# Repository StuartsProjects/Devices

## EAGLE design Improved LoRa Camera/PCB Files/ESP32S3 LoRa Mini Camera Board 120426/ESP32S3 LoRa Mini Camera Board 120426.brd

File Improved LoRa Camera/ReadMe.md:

This is a repository for information on improved LoRa Camera boards. 

### Stuart Robinson

### April 2026

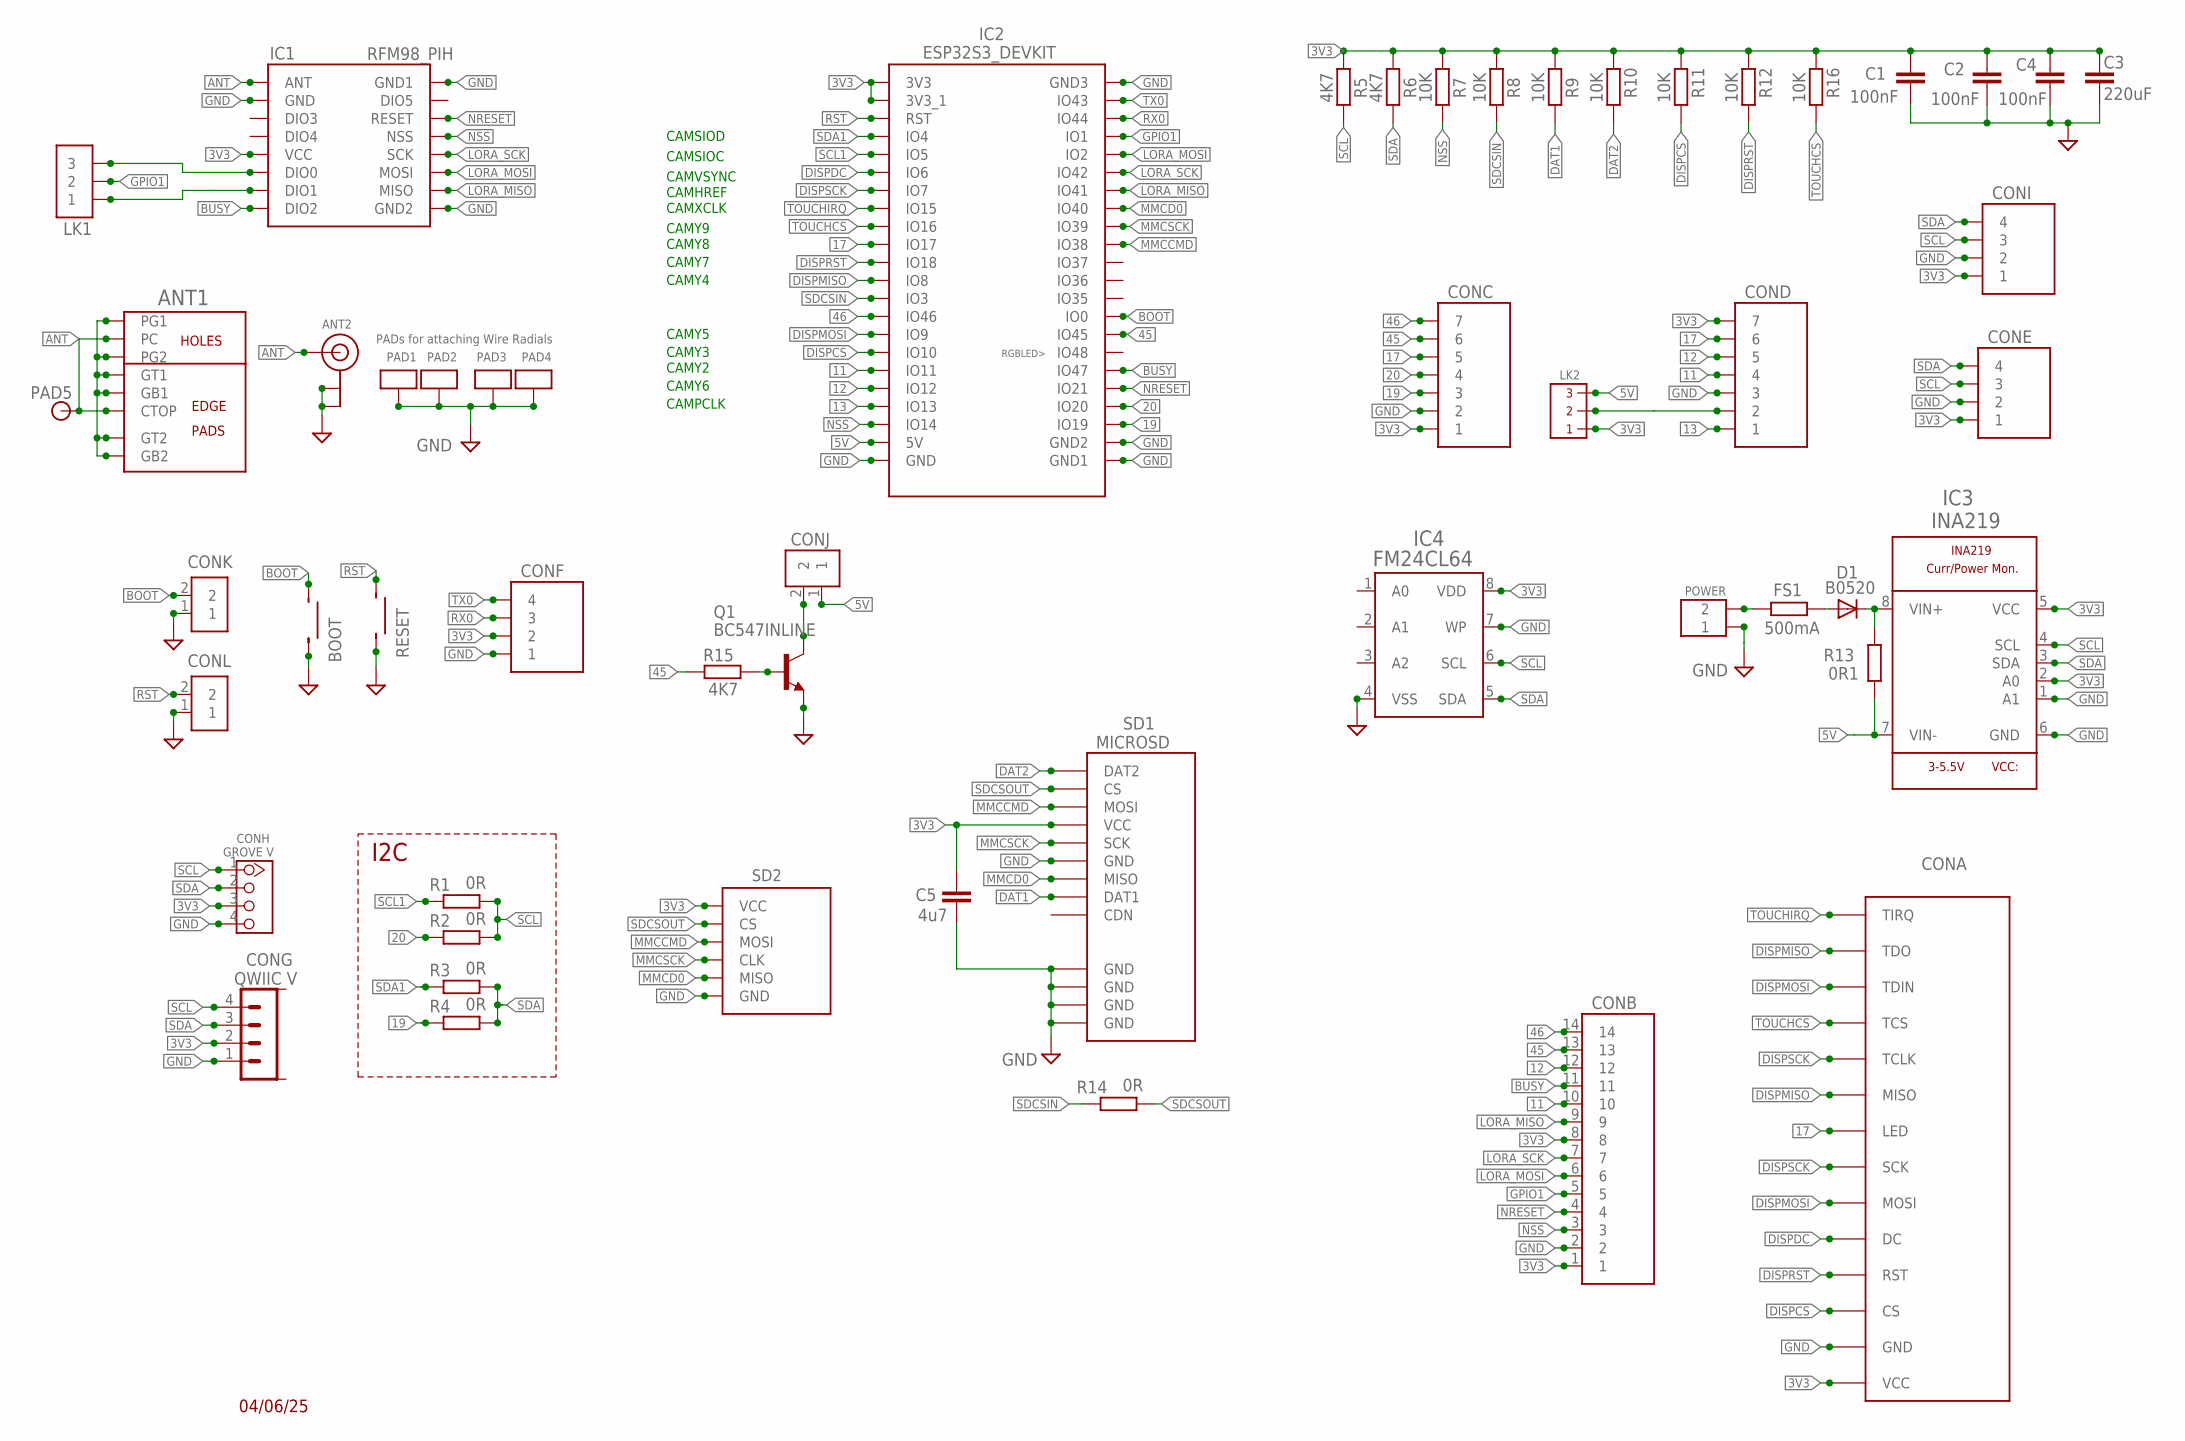
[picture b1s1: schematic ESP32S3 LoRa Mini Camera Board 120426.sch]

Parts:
ANT1: CUSTOMSMA
ANT2: ANTENNA_U.FL; U.FL
BOOT: SMALLSMTSWITCH
C1, C2, C4: 100nF; C1206
C3: 220uF; C1210K
C5: 4u7; C1206
CONA: ILI9341; ILI9341_2_4_INCH_NOSD
CONB: 14X1
CONC: 7X1STD; 7X1
COND: 7X1STD; 7X1
CONE: 4X1
CONF: 4X1
CONG: QWIIC V; BM04B-SRSS-TB
CONH: GROVE V; HW4-2.0
CONI: 4X1
CONJ: 2X1
CONK: 2X1
CONL: 2X1
D1: B0520; SOD123
FS1: 500mA; M1206
IC1: RFM98_PIH
IC2: ESP32S3_DEVKIT
IC3: INA219; SOIC8
IC4: FM24CL64; SOIC_2
LK1: 3X1
LK2: 3PINMICROHEADER_ROUND2; 3PINMICROHEADER_SMALL_ROUND_2
PAD1, PAD2, PAD3, PAD4: ANTPAD2
PAD5: PAD_ROUND_0_6MM_HOLE; PAD-ROUND_0_6MM_HOLE
POWER: SCREWTERMINAL_2WAY_0_1_INCH
Q1: BC547INLINE; TO92-CBE
R1, R2, R3, R4, R14: 0R; M1206
R5, R6, R15: 4K7; M1206
R7, R8, R9, R10, R11, R12, R16: 10K; M1206
R13: 0R1; R1206
RESET: SMALLSMTSWITCH
SD1: MICROSD; MICROSD_PP
SD2: MICROSD_BREAKOUT2_DEFAULT; MICROSD_BREAKOUT2

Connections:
3V3: C1.2, C2.2, C3.1, C4.2, C5.1, CONA.VCC, CONB.1, CONB.8, CONC.1, COND.7, CONE.1, CONF.2, CONG.2, CONH.3, CONI.1, IC1.VCC, IC2.3V3, IC2.3V3_1, IC3.2 (A0), IC3.5 (VCC), IC4.8 (VDD), LK2.1, R5.2, R6.2, R7.2, R8.2, R9.2, R10.2, R11.2, R12.2, R16.2, SD1.VCC, SD2.VCC
5V: CONJ.1, IC2.5V, IC3.7 (VIN-), LK2.3, R13.1
11: CONB.10, COND.4, IC2.11 (IO11)
12: CONB.12, COND.5, IC2.12 (IO12)
13: COND.1, IC2.13 (IO13)
17: CONA.LED, CONC.5, COND.6, IC2.17 (IO17)
19: CONC.3, IC2.19 (IO19), R4.2
20: CONC.4, IC2.20 (IO20), R2.2
45: CONB.13, CONC.6, IC2.45 (IO45), R15.2
46: CONB.14, CONC.7, IC2.46 (IO46)
ANT: ANT1.CTOP, ANT1.PC, ANT2.3 (SIGNAL), IC1.ANT, PAD5.P$1
BOOT: BOOT.P$4, CONK.2, IC2.0 (IO0)
BUSY: CONB.11, IC1.DIO2, IC2.47 (IO47)
DAT1: R9.1, SD1.DAT1
DAT2: R10.1, SD1.DAT2
DISPCS: CONA.CS, IC2.10 (IO10), R11.1
DISPDC: CONA.DC, IC2.6 (IO6)
DISPMISO: CONA.MISO, CONA.TDO, IC2.8 (IO8)
DISPMOSI: CONA.MOSI, CONA.TDIN, IC2.9 (IO9)
DISPRST: CONA.RST, IC2.18 (IO18), R12.1
DISPSCK: CONA.SCK, CONA.TCLK, IC2.7 (IO7)
GND: ANT1.G1, ANT1.G2, ANT1.GB1, ANT1.GB2, ANT1.GT1, ANT1.GT2, ANT2.1 (GND), ANT2.2 (GND), BOOT.P$3, C1.1, C2.1, C3.2, C4.1, C5.2, CONA.GND, CONB.2, CONC.2, COND.3, CONE.2, CONF.1, CONG.1, CONH.4, CONI.2, CONK.1, CONL.1, IC1.GND, IC1.GND1, IC1.GND2, IC2.GND, IC2.GND1, IC2.GND2, IC2.GND3, IC3.1 (A1), IC3.6 (GND), IC4.4 (VSS), IC4.7 (WP), PAD1.P$1, PAD2.P$1, PAD3.P$1, PAD4.P$1, POWER.P$1 (1), Q1.E, RESET.P$3, SD1.GND, SD1.GND@1 (GND), SD1.GND@2 (GND), SD1.GND@3 (GND), SD1.GND@4 (GND), SD2.GND
GPIO1: CONB.5, IC2.1 (IO1), LK1.2
LORA_MISO: CONB.9, IC1.MISO, IC2.41 (IO41)
LORA_MOSI: CONB.6, IC1.MOSI, IC2.2 (IO2)
LORA_SCK: CONB.7, IC1.SCK, IC2.42 (IO42)
MMCCMD: IC2.38 (IO38), SD1.MOSI, SD2.MOSI
MMCD0: IC2.40 (IO40), SD1.MISO, SD2.MISO
MMCSCK: IC2.39 (IO39), SD1.SCK, SD2.SCK (CLK)
unnamed: D1.C, IC3.8 (VIN+), R13.2
unnamed: IC1.DIO0, LK1.3
unnamed: FS1.1, POWER.P$2 (2)
unnamed: IC1.DIO1, LK1.1
unnamed: D1.A, FS1.2
unnamed: Q1.B, R15.1
unnamed: CONJ.2, Q1.C
unnamed: COND.2, LK2.2
NRESET: CONB.4, IC1.RESET, IC2.21 (IO21)
NSS: CONB.3, IC1.NSS, IC2.14 (IO14), R7.1
RST: CONL.2, IC2.RST, RESET.P$4
RX0: CONF.3, IC2.44 (IO44)
SCL: CONE.3, CONG.4, CONH.1, CONI.3, IC3.4 (SCL), IC4.6 (SCL), R1.1, R2.1, R5.1
SCL1: IC2.5 (IO5), R1.2
SDA: CONE.4, CONG.3, CONH.2, CONI.4, IC3.3 (SDA), IC4.5 (SDA), R3.1, R4.1, R6.1
SDA1: IC2.4 (IO4), R3.2
SDCSIN: IC2.3 (IO3), R8.1, R14.2
SDCSOUT: R14.1, SD1.CS, SD2.CS
TOUCHCS: CONA.TCS, IC2.16 (IO16), R16.1
TOUCHIRQ: CONA.TIRQ, IC2.15 (IO15)
TX0: CONF.4, IC2.43 (IO43)

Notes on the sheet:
04/06/25
PADs for attaching Wire Radials
CAMSIOD
CAMSIOC
CAMVSYNC
CAMHREF
CAMXCLK
CAMY9
CAMY8
CAMY7
CAMY4
CAMY5
CAMY3
CAMY2
CAMY6
CAMPCLK
I2C

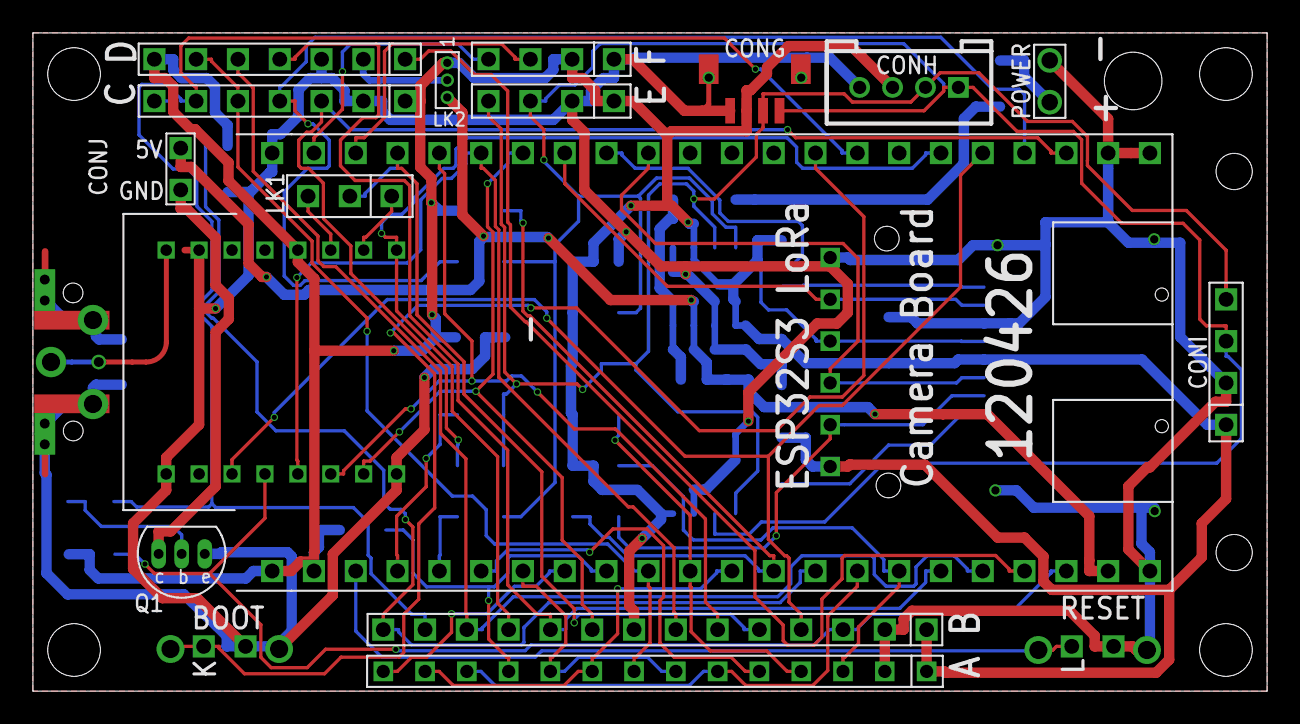
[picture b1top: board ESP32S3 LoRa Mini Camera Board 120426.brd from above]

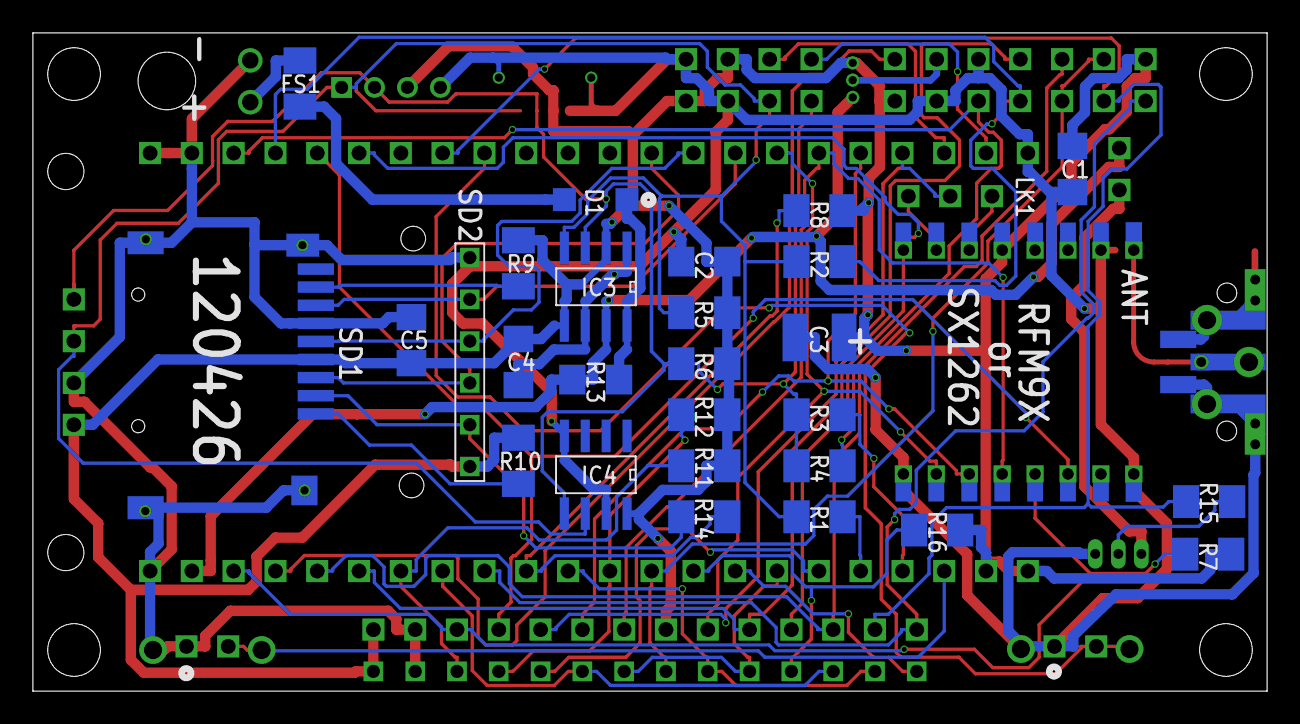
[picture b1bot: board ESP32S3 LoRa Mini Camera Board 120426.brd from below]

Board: 2 copper layers, 75.0 x 40.0 mm, 54 parts (30 on the bottom side), 50 nets.

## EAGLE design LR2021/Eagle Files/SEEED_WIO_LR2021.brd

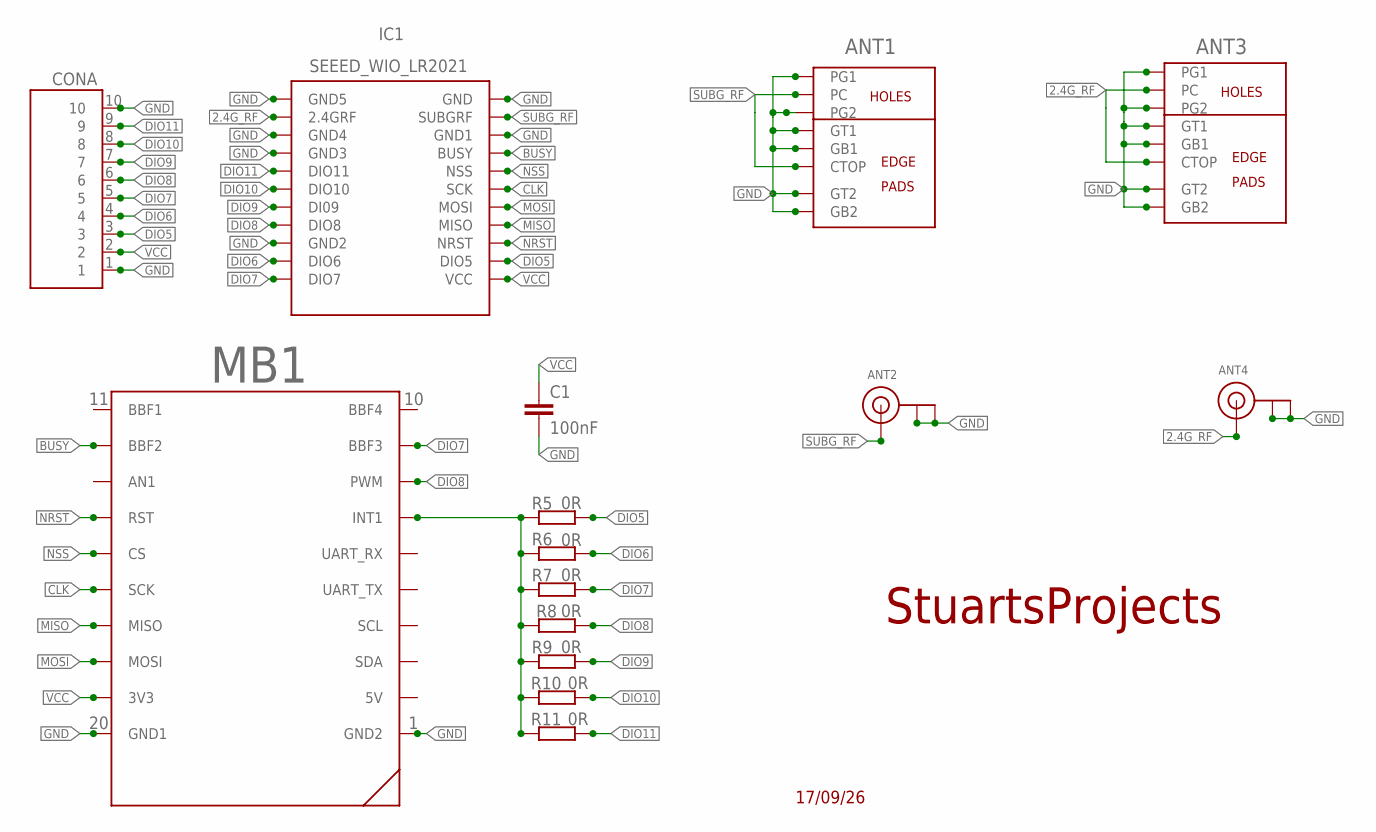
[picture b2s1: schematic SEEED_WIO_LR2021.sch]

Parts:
ANT1, ANT3: CUSTOMSMA
ANT2, ANT4: ANTENNA_U.FL; U.FL
C1: 100nF; C0805
CONA: 10X1
IC1: SEEED_WIO_LR2021; LR2021_SEEED
MB1: BBFRIENDY2; PCB_SOCKET_BBFRIENDLY2
R5, R6, R7, R8, R9, R10, R11: 0R; R0805

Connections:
2.4G_RF: ANT3.CTOP, ANT3.PC, ANT4.3 (SIGNAL), IC1.P$13 (2.4GRF)
BUSY: IC1.P$8 (BUSY), MB1.BBF2
CLK: IC1.P$6 (SCK), MB1.SCK
DIO5: CONA.3, IC1.P$2 (DIO5), R5.1
DIO6: CONA.4, IC1.P$21 (DIO6), R6.1
DIO7: CONA.5, IC1.P$22 (DIO7), MB1.BBF3, R7.1
DIO8: CONA.6, IC1.P$19 (DIO8), MB1.PWM, R8.1
DIO9: CONA.7, IC1.P$18 (DI09), R9.1
DIO10: CONA.8, IC1.P$17 (DIO10), R10.1
DIO11: CONA.9, IC1.P$16 (DIO11), R11.1
GND: ANT1.G1, ANT1.G2, ANT1.GB1, ANT1.GB2, ANT1.GT1, ANT1.GT2, ANT2.1 (GND), ANT2.2 (GND), ANT3.G1, ANT3.G2, ANT3.GB1, ANT3.GB2, ANT3.GT1, ANT3.GT2, ANT4.1 (GND), ANT4.2 (GND), C1.2, CONA.1, CONA.10, IC1.P$9 (GND1), IC1.P$11 (GND), IC1.P$12 (GND5), IC1.P$14 (GND4), IC1.P$15 (GND3), IC1.P$20 (GND2), MB1.GND1 (GND2), MB1.GND2 (GND1)
IRQ: MB1.INT (INT1), R5.2, R6.2, R7.2, R8.2, R9.2, R10.2, R11.2
MISO: IC1.P$4 (MISO), MB1.MISO
MOSI: IC1.P$5 (MOSI), MB1.MOSI
NRST: IC1.P$3 (NRST), MB1.RST
NSS: IC1.P$7 (NSS), MB1.CS
SUBG_RF: ANT1.CTOP, ANT1.PC, ANT2.3 (SIGNAL), IC1.P$10 (SUBGRF)
VCC: C1.1, CONA.2, IC1.P$1 (VCC), MB1.3V3

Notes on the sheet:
17/09/26
StuartsProjects

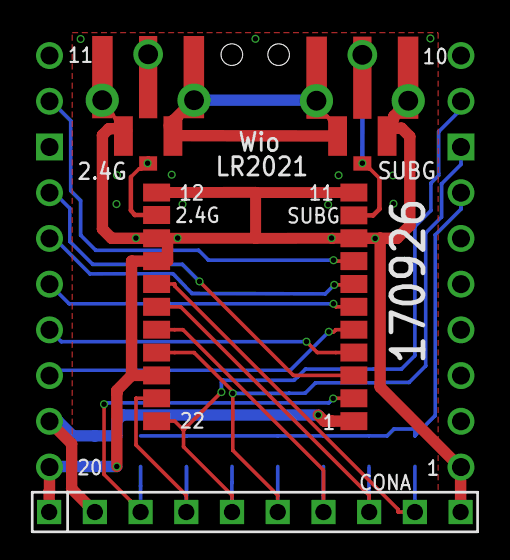
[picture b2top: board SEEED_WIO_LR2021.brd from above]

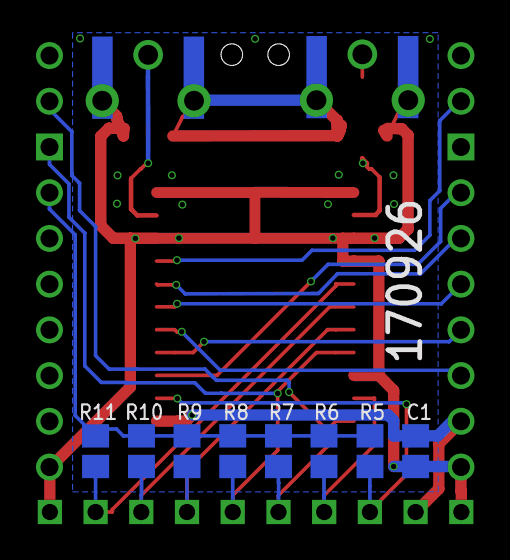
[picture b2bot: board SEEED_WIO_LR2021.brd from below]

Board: 2 copper layers, 15 parts (8 on the bottom side), 18 nets.

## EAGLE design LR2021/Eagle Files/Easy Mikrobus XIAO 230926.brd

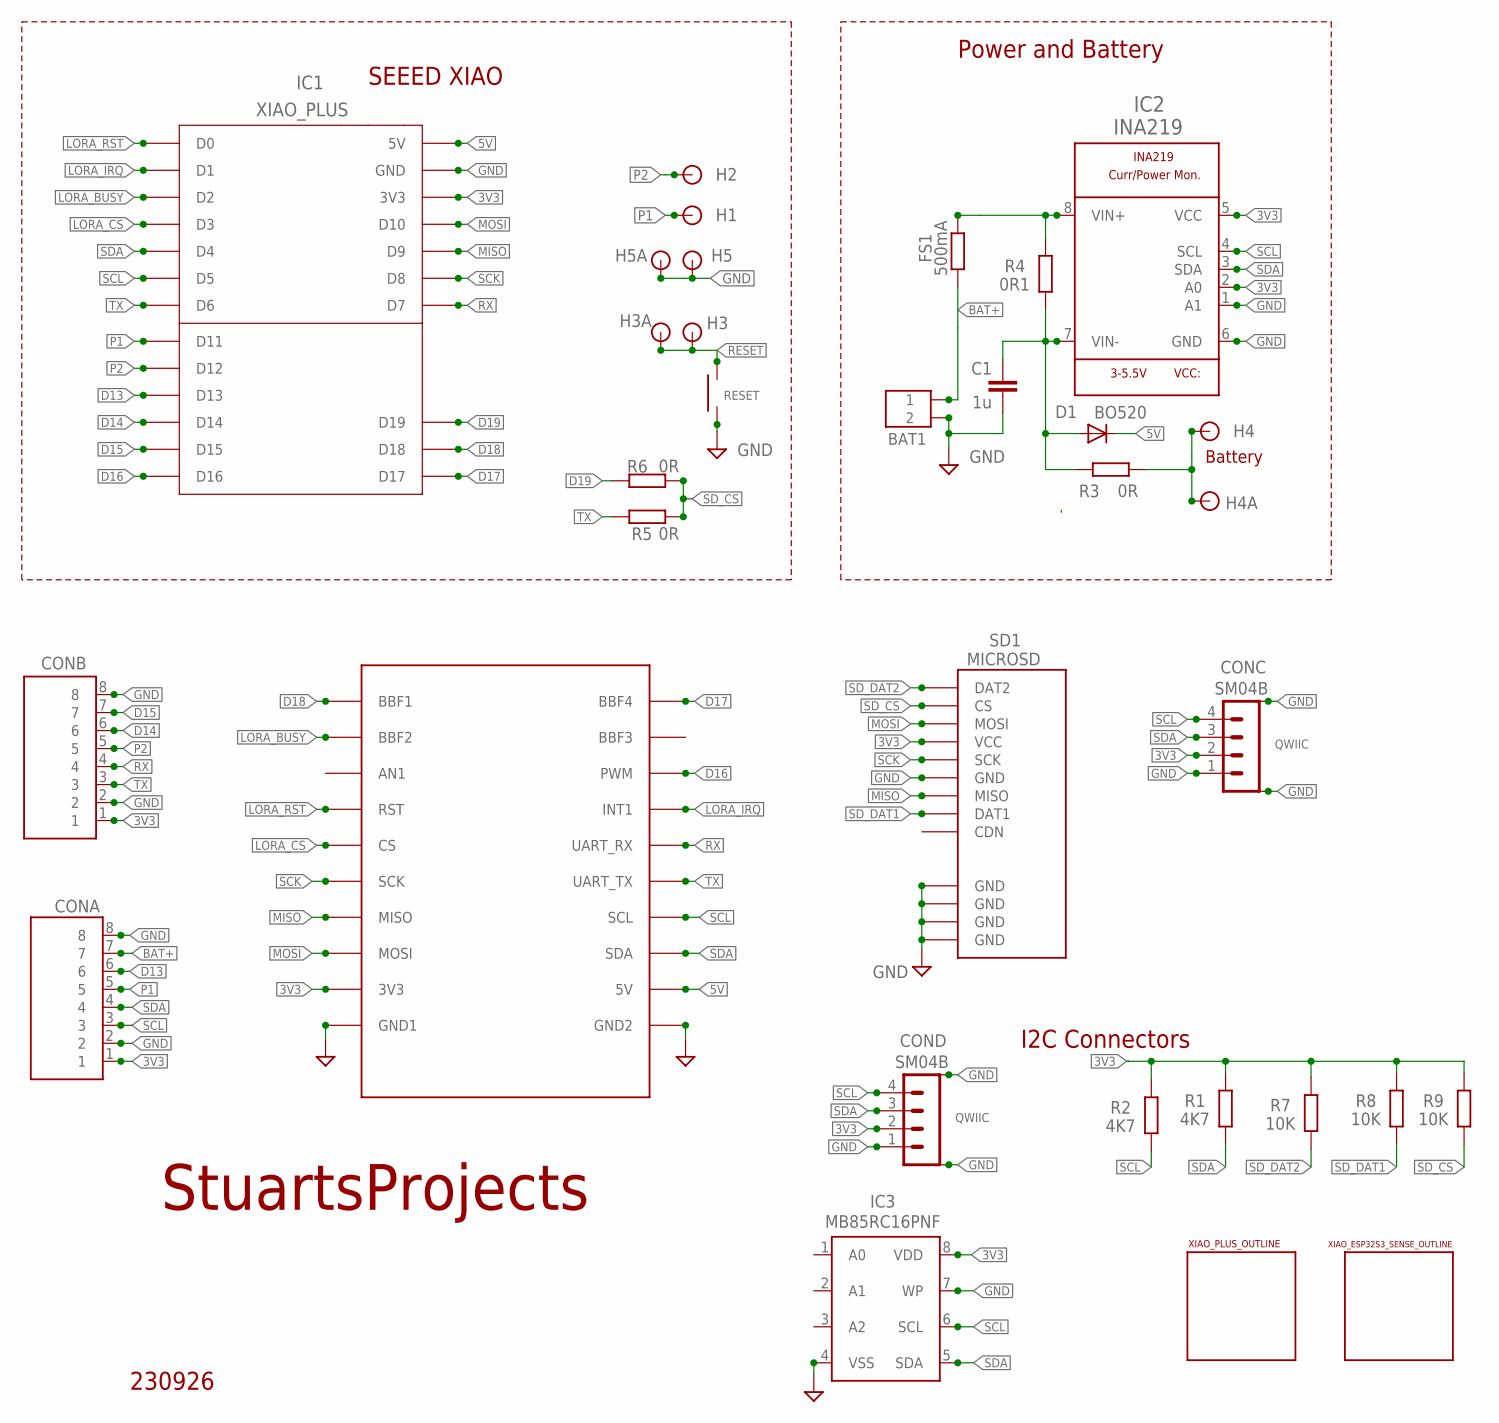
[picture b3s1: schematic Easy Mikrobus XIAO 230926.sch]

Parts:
BAT1: SCREWTERMINAL_2WAY_0_1_INCH
C1: 1u; C1206
CONA: 8X1
CONB: 8X1
CONC: SM04B; SM04B-SRSS-TB
COND: SM04B; SM04B-SRSS-TB
D1: BO520; SOD123
FS1: 500mA; R1206
H1, H2, H3, H3A, H4, H4A, H5, H5A: PAD_ROUND_0_8MM_HOLE
IC1: XIAO_PLUS; PLUS_PIH
IC2: INA219; SOIC8
IC3: MB85RC16PNF; SOIC_2
MB1: BBFRIENDY2; PCB_SOCKET_BBFRIENDLY2
R1, R2: 4K7; R1206
R3, R5, R6: 0R; R1206
R4: 0R1; R1206
R7, R8, R9: 10K; R1206
RESET: SMTSWITCH_4_X_3
SD1: MICROSD; MICROSD_PP
U$3: ESP32S3_SENSE_OUTLINE_DEFAULT; ESP32S3_SENSE_OUTLINE
U$4: PLUS_OUTLINE_ALL; PLUS_OUTLINE

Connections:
3V3: CONA.1, CONB.1, CONC.2, COND.2, IC1.3V3.1 (3V3), IC1.3V3.2 (3V3), IC2.2 (A0), IC2.5 (VCC), IC3.8 (VDD), MB1.3V3, R1.2, R2.2, R7.2, R8.2, R9.2, SD1.VCC
5V: D1.C, IC1.5V.1 (5V), IC1.5V.2 (5V), MB1.5V
BAT+: BAT1.P$1 (1), CONA.7, FS1.2
D13: CONA.6, IC1.D13
D14: CONB.6, IC1.D14
D15: CONB.7, IC1.D15
D16: IC1.D16, MB1.PWM
D17: IC1.D17, MB1.BBF4
D18: IC1.D18, MB1.BBF1
D19: IC1.D19, R6.2
GND: BAT1.P$2 (2), C1.2, CONA.2, CONA.8, CONB.2, CONB.8, CONC.1, CONC.M1, CONC.M2, COND.1, COND.M1, COND.M2, H5.P$1, H5A.P$1, IC1.GND.1 (GND), IC1.GND.2 (GND), IC2.1 (A1), IC2.6 (GND), IC3.4 (VSS), IC3.7 (WP), MB1.GND1 (GND2), MB1.GND2 (GND1), RESET.1, SD1.GND, SD1.GND@1 (GND), SD1.GND@2 (GND), SD1.GND@3 (GND), SD1.GND@4 (GND)
LORA_BUSY: IC1.D2.1 (D2), IC1.D2.2 (D2), MB1.BBF2
LORA_CS: IC1.D3.1 (D3), IC1.D3.2 (D3), MB1.CS
LORA_IRQ: IC1.D1.1 (D1), IC1.D1.2 (D1), MB1.INT (INT1)
LORA_RST: IC1.D0.1 (D0), IC1.D0.2 (D0), MB1.RST
MISO: IC1.D9.1 (D9), IC1.D9.2 (D9), MB1.MISO, SD1.MISO
MOSI: IC1.D10.1 (D10), IC1.D10.2 (D10), MB1.MOSI, SD1.MOSI
P1: CONA.5, H1.P$1, IC1.D11
P2: CONB.5, H2.P$1, IC1.D12
PIN: H4.P$1, H4A.P$1, R3.1
RESET: H3.P$1, H3A.P$1, RESET.2
RX: CONB.4, IC1.D7.1 (D7), IC1.D7.2 (D7), MB1.RX (UART_RX)
SCK: IC1.D8.1 (D8), IC1.D8.2 (D8), MB1.SCK, SD1.SCK
SCL: CONA.3, CONC.4, COND.4, IC1.D5.1 (D5), IC1.D5.2 (D5), IC2.4 (SCL), IC3.6 (SCL), MB1.SCL, R2.1
SDA: CONA.4, CONC.3, COND.3, IC1.D4.1 (D4), IC1.D4.2 (D4), IC2.3 (SDA), IC3.5 (SDA), MB1.SDA, R1.1
SD_CS: R5.1, R6.1, R9.1, SD1.CS
SD_DAT1: R8.1, SD1.DAT1
SD_DAT2: R7.1, SD1.DAT2
TX: CONB.3, IC1.D6.1 (D6), IC1.D6.2 (D6), MB1.TX (UART_TX), R5.2
VIN: C1.1, D1.A, IC2.7 (VIN-), R3.2, R4.1
VIN+: FS1.1, IC2.8 (VIN+), R4.2

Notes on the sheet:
230926
StuartsProjects
SEEED XIAO
Battery
Power and Battery
QWIIC
I2C Connectors

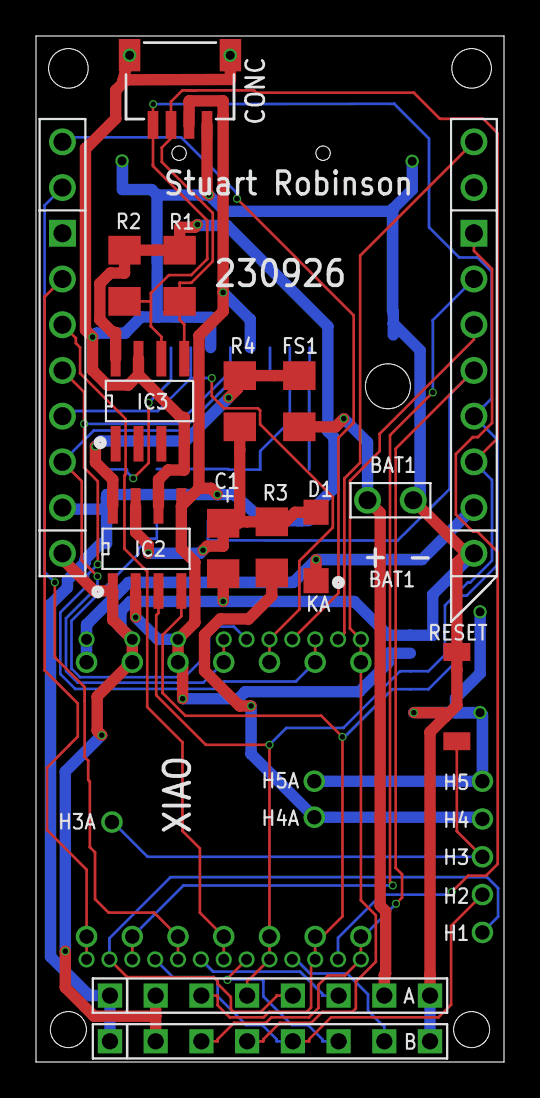
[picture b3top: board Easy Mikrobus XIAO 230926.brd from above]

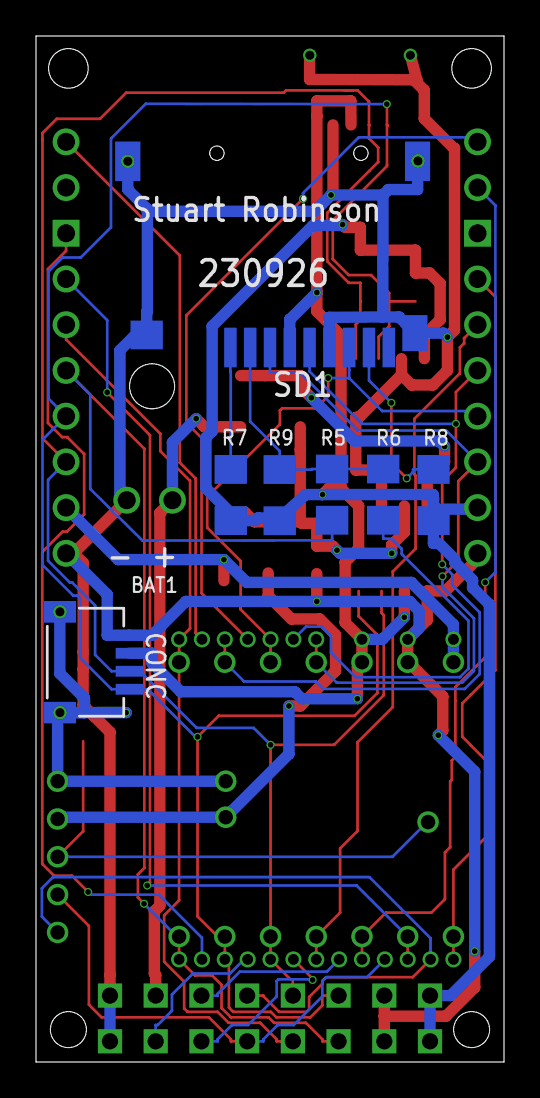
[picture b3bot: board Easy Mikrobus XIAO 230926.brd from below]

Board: 2 copper layers, 26.0 x 57.0 mm, 33 parts (7 on the bottom side), 31 nets.

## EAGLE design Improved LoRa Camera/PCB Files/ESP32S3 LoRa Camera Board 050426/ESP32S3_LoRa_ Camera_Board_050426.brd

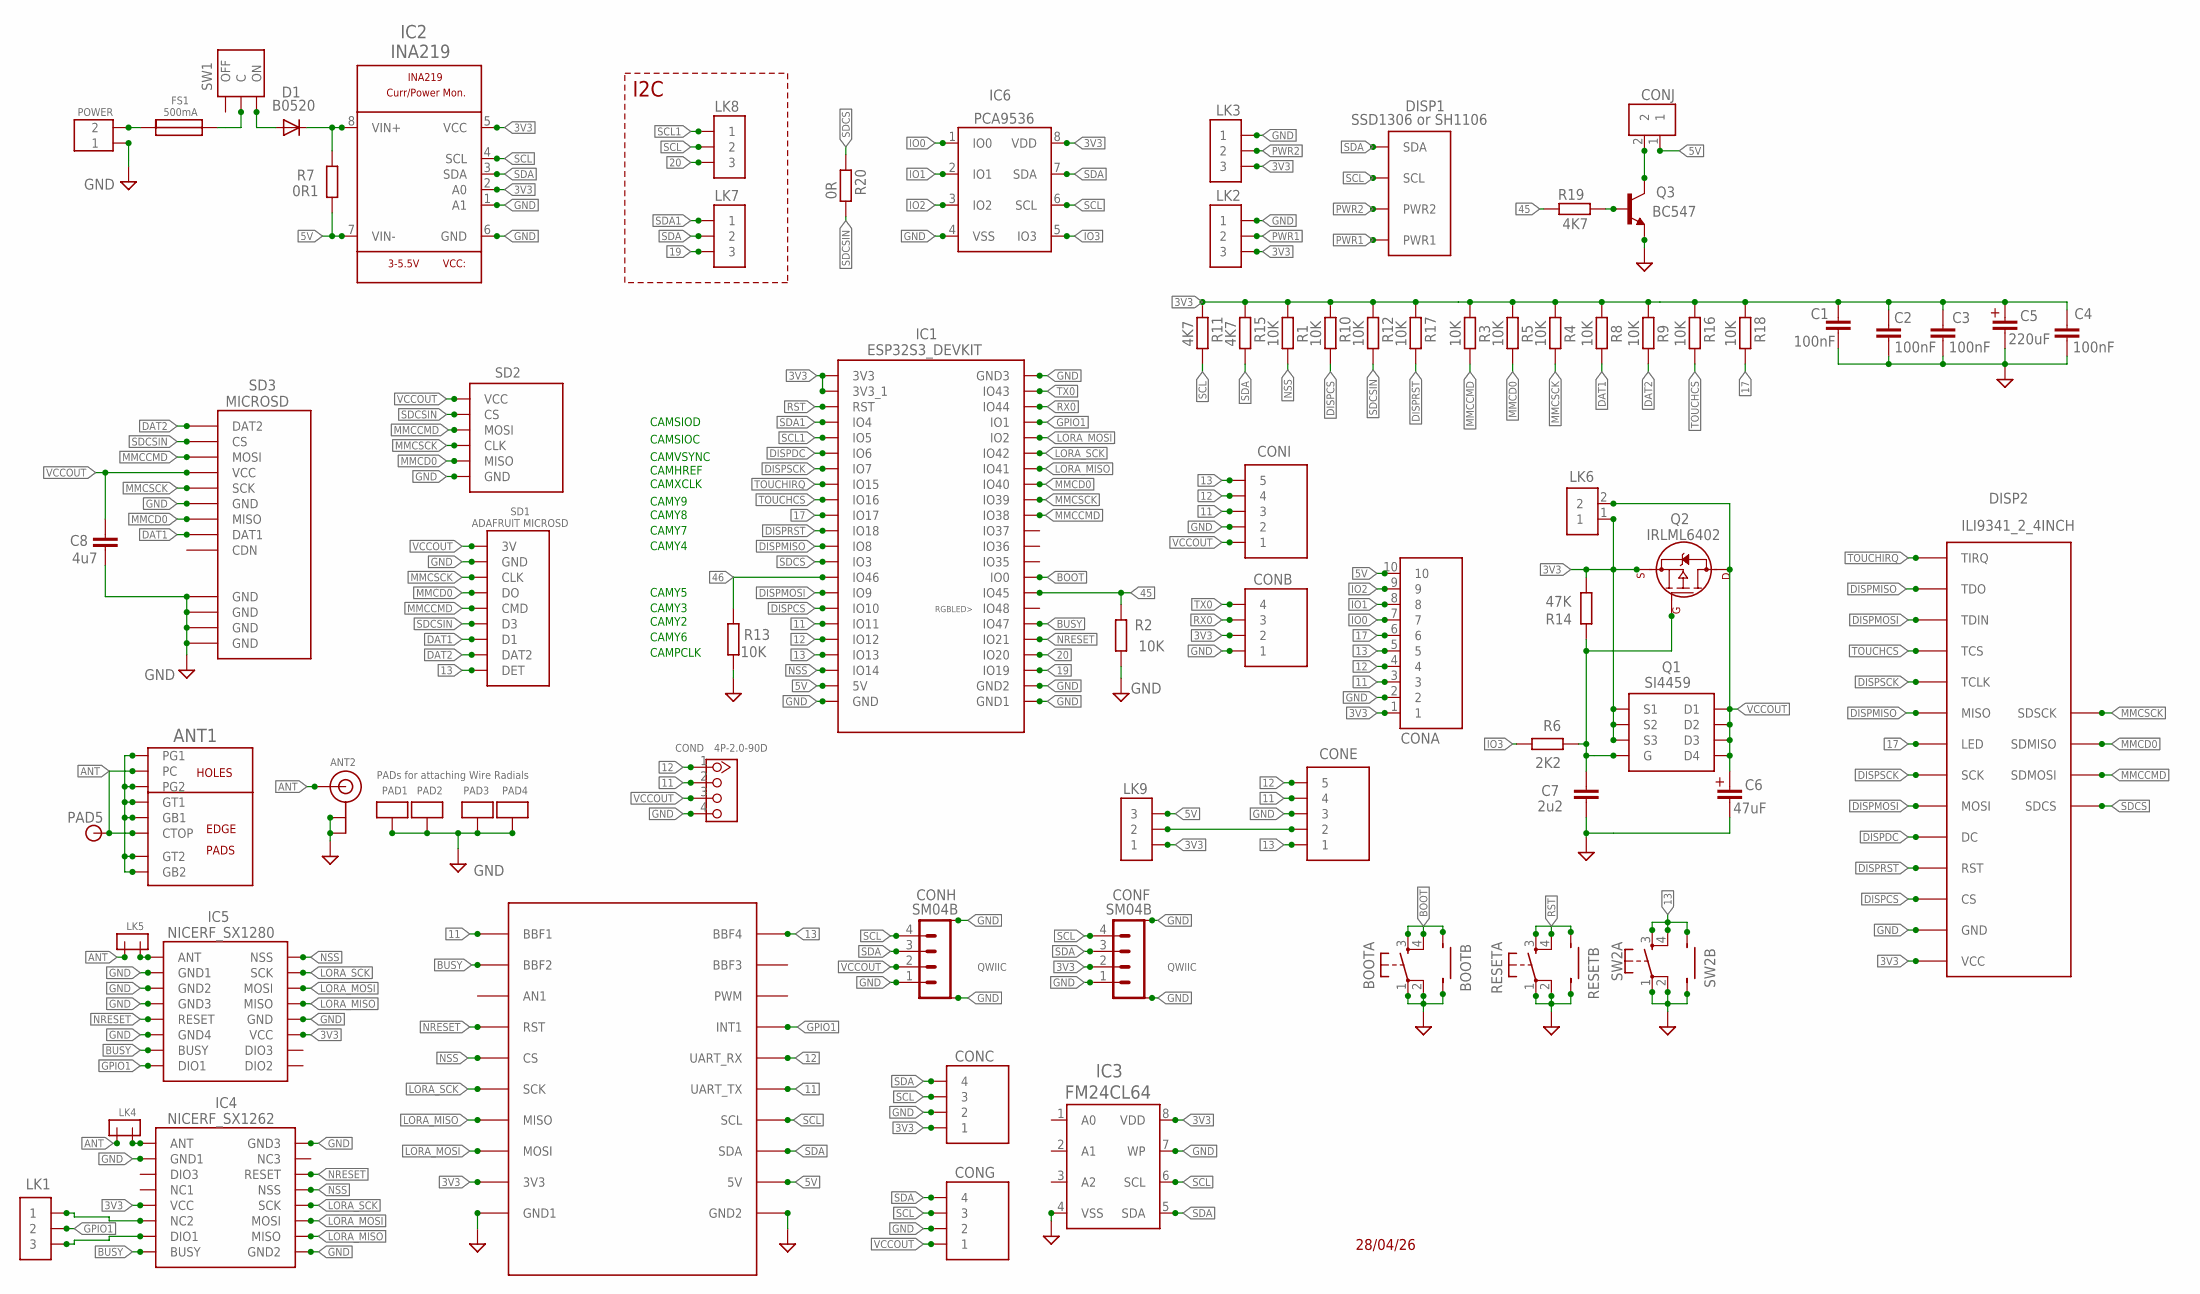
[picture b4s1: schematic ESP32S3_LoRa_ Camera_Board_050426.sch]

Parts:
ANT1: CUSTOMSMA
ANT2: ANTENNA_U.FL; U.FL
BOOTA: DTS-6
BOOTB: SMALLSMTSWITCH
C1, C2, C3, C4: 100nF; MEDIUM_CERAMIC_DISC
C5: 220uF; 2.5MM_SPACING_CAPACITOR
C6: 47uF; 2.5MM_SPACING_CAPACITOR
C7: 2u2; C1206
C8: 4u7; C1206
CONA: 10X1
CONB: 4X1
CONC: 4X1
COND: 4P-2.0-90D; HW4-2.0-90D
CONE: 5X1
CONF: SM04B; SM04B-SRSS-TB
CONG: 4X1
CONH: SM04B; SM04B-SRSS-TB
CONI: 5X1
CONJ: 2X1
D1: B0520; SOD123
DISP1: SSD1306 or SH1106; SMALL_OLED2
DISP2: ILI9341_2_4INCH; ILI9341_2_4_INCH
FS1: 500mA; SMALL_POLYFUSE
IC1: ESP32S3_DEVKIT
IC2: INA219; SOIC8
IC3: FM24CL64; SOIC_2
IC4: NICERF_SX1262
IC5: NICERF_SX1280
IC6: PCA9536; SOIC08
LK1: 3X1_SMALL_ROUND_PAD
LK2, LK3, LK7, LK8, LK9: 3X1
LK4, LK5: 2PINMICROHEADER
LK6: 2X1_SMALL_ROUND_PAD
MB1: BBFRIENDY2; PCB_SOCKET_BBFRIENDLY2
PAD1, PAD2, PAD3, PAD4: ANTPAD2
PAD5: PAD_ROUND_0_6MM_HOLE; PAD-ROUND_0_6MM_HOLE
POWER: SCREWTERMINAL_2WAY_0_1_INCH
Q1: SI4459; SOIC_2
Q2: IRLML6402; SOT23
Q3: BC547; TO92-CBE
R1, R2, R3, R4, R5, R8, R9, R10, R12, R13, R16, R17, R18: 10K; R1206
R6: 2K2; R1206
R7: 0R1; R1206
R11, R15: 4K7; R1206
R14: 47K; R1206
R19: 4K7; M1206
R20: 0R; R1206
RESETA: DTS-6
RESETB: SMALLSMTSWITCH
SD1: ADAFRUIT MICROSD; ADAFRUIT_MICROSD
SD2: MICROSD_BREAKOUT2_DEFAULT; MICROSD_BREAKOUT2
SD3: MICROSD; MICROSD_PP
SW1: PCB_SLIDE_SWITCH2; SK12F14
SW2A: DTS-6
SW2B: SMALLSMTSWITCH

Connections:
3V3: C1.2, C2.2, C3.2, C4.2, C5.+, CONA.1, CONB.2, CONC.1, CONF.2, DISP2.VCC, IC1.3V3, IC1.3V3_1, IC2.2 (A0), IC2.5 (VCC), IC3.8 (VDD), IC4.P$5 (VCC), IC5.P$3 (VCC), IC6.8 (VDD), LK2.3, LK3.3, LK6.1, LK9.1, MB1.3V3, Q1.1 (S1), Q1.2 (S2), Q1.3 (S3), Q2.2 (S1), R1.2, R3.2, R4.2, R5.2, R8.2, R9.2, R10.2, R11.2, R12.2, R14.1, R15.2, R16.2, R17.2, R18.2
5V: CONA.10, CONJ.1, IC1.5V, IC2.7 (VIN-), LK9.3, MB1.5V, R7.1
11: CONA.3, COND.2, CONE.4, CONI.3, IC1.11 (IO11), MB1.BBF1, MB1.TX (UART_TX)
12: CONA.4, COND.1, CONE.5, CONI.4, IC1.12 (IO12), MB1.RX (UART_RX)
13: CONA.5, CONE.1, CONI.5, IC1.13 (IO13), MB1.BBF4, SD1.P$9 (DET), SW2A.3, SW2A.4, SW2B.P$4
17: CONA.6, DISP2.LED, IC1.17 (IO17), R18.1
19: IC1.19 (IO19), LK7.3
20: IC1.20 (IO20), LK8.3
45: IC1.45 (IO45), R2.1, R19.2
46: IC1.46 (IO46), R13.2
ANT: ANT1.CTOP, ANT1.PC, ANT2.3 (SIGNAL), LK4.1, LK5.1, PAD5.P$1
BOOT: BOOTA.3, BOOTA.4, BOOTB.P$4, IC1.0 (IO0)
BUSY: IC1.47 (IO47), IC4.P$8 (BUSY), IC5.P$15 (BUSY), MB1.BBF2
DAT1: R8.1, SD1.P$7 (D1), SD3.DAT1
DAT2: R9.1, SD1.P$8 (DAT2), SD3.DAT2
DISPCS: DISP2.CS, IC1.10 (IO10), R10.1
DISPDC: DISP2.DC, IC1.6 (IO6)
DISPMISO: DISP2.MISO, DISP2.TDO, IC1.8 (IO8)
DISPMOSI: DISP2.MOSI, DISP2.TDIN, IC1.9 (IO9)
DISPRST: DISP2.RST, IC1.18 (IO18), R17.1
DISPSCK: DISP2.SCK, DISP2.TCLK, IC1.7 (IO7)
GND: ANT1.G1, ANT1.G2, ANT1.GB1, ANT1.GB2, ANT1.GT1, ANT1.GT2, ANT2.1 (GND), ANT2.2 (GND), BOOTA.1, BOOTA.2, BOOTB.P$3, C1.1, C2.1, C3.1, C4.1, C5.-, C6.-, C7.2, C8.2, CONA.2, CONB.1, CONC.2, COND.4, CONE.3, CONF.1, CONF.M1, CONF.M2, CONG.2, CONH.1, CONH.M1, CONH.M2, CONI.2, DISP2.GND, IC1.GND, IC1.GND1, IC1.GND2, IC1.GND3, IC2.1 (A1), IC2.6 (GND), IC3.4 (VSS), IC3.7 (WP), IC4.P$2 (GND1), IC4.P$9 (GND2), IC4.P$16 (GND3), IC5.P$4 (GND), IC5.P$10 (GND1), IC5.P$11 (GND2), IC5.P$12 (GND3), IC5.P$14 (GND4), IC6.4 (VSS), LK2.1, LK3.1, MB1.GND1 (GND2), MB1.GND2 (GND1), PAD1.P$1, PAD2.P$1, PAD3.P$1, PAD4.P$1, POWER.P$1 (1), Q3.E, R2.2, R13.1, RESETA.1, RESETA.2, RESETB.P$3, SD1.P$2 (GND), SD2.GND, SD3.GND, SD3.GND@1 (GND), SD3.GND@2 (GND), SD3.GND@3 (GND), SD3.GND@4 (GND), SW2A.1, SW2A.2, SW2B.P$3
GPIO1: IC1.1 (IO1), IC5.P$16 (DIO1), LK1.2, MB1.INT (INT1)
IO0: CONA.7, IC6.1 (IO0)
IO1: CONA.8, IC6.2 (IO1)
IO2: CONA.9, IC6.3 (IO2)
IO3: IC6.5 (IO3), R6.2
LORA_MISO: IC1.41 (IO41), IC4.P$10 (MISO), IC5.P$5 (MISO), MB1.MISO
LORA_MOSI: IC1.2 (IO2), IC4.P$11 (MOSI), IC5.P$6 (MOSI), MB1.MOSI
LORA_SCK: IC1.42 (IO42), IC4.P$12 (SCK), IC5.P$7 (SCK), MB1.SCK
MMCCMD: DISP2.SDMOSI, IC1.38 (IO38), R3.1, SD1.P$5 (CMD), SD2.MOSI, SD3.MOSI
MMCD0: DISP2.SDMISO, IC1.40 (IO40), R5.1, SD1.P$4 (DO), SD2.MISO, SD3.MISO
MMCSCK: DISP2.SDSCK, IC1.39 (IO39), R4.1, SD1.P$3 (CLK), SD2.SCK (CLK), SD3.SCK
unnamed: C7.1, Q1.4 (G), Q2.1 (G1), R6.1, R14.2
unnamed: IC4.P$6 (NC2), LK1.1
unnamed: IC5.P$9 (ANT), LK5.2
unnamed: IC4.P$7 (DIO1), LK1.3
unnamed: IC4.P$1 (ANT), LK4.2
unnamed: D1.C, IC2.8 (VIN+), R7.2
unnamed: FS1.P$1, POWER.P$2 (2)
unnamed: D1.A, SW1.ON
unnamed: Q3.B, R19.1
unnamed: FS1.P$2, SW1.C
unnamed: CONJ.2, Q3.C
unnamed: CONE.2, LK9.2
NRESET: IC1.21 (IO21), IC4.P$14 (RESET), IC5.P$13 (RESET), MB1.RST
NSS: IC1.14 (IO14), IC4.P$13 (NSS), IC5.P$8 (NSS), MB1.CS, R1.1
PWR1: DISP1.1 (PWR1), LK2.2
PWR2: DISP1.2 (PWR2), LK3.2
RST: IC1.RST, RESETA.3, RESETA.4, RESETB.P$4
RX0: CONB.3, IC1.44 (IO44)
SCL: CONC.3, CONF.4, CONG.3, CONH.4, DISP1.SCL, IC2.4 (SCL), IC3.6 (SCL), IC6.6 (SCL), LK8.2, MB1.SCL, R11.1
SCL1: IC1.5 (IO5), LK8.1
SDA: CONC.4, CONF.3, CONG.4, CONH.3, DISP1.SDA, IC2.3 (SDA), IC3.5 (SDA), IC6.7 (SDA), LK7.2, MB1.SDA, R15.1
SDA1: IC1.4 (IO4), LK7.1
SDCS: DISP2.SDCS, IC1.3 (IO3), R20.2
SDCSIN: R12.1, R20.1, SD1.P$6 (D3), SD2.CS, SD3.CS
TOUCHCS: DISP2.TCS, IC1.16 (IO16), R16.1
TOUCHIRQ: DISP2.TIRQ, IC1.15 (IO15)
TX0: CONB.4, IC1.43 (IO43)
VCCOUT: C6.+, C8.1, COND.3, CONG.1, CONH.2, CONI.1, LK6.2, Q1.5 (D4), Q1.6 (D3), Q1.7 (D2), Q1.8 (D1), Q2.3 (D1), SD1.P$1 (3V), SD2.VCC, SD3.VCC

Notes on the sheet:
28/04/26
PADs for attaching Wire Radials
QWIIC
CAMSIOD
CAMSIOC
CAMVSYNC
CAMHREF
CAMXCLK
CAMY9
CAMY8
CAMY7
CAMY4
CAMY5
CAMY3
CAMY2
CAMY6
CAMPCLK
I2C

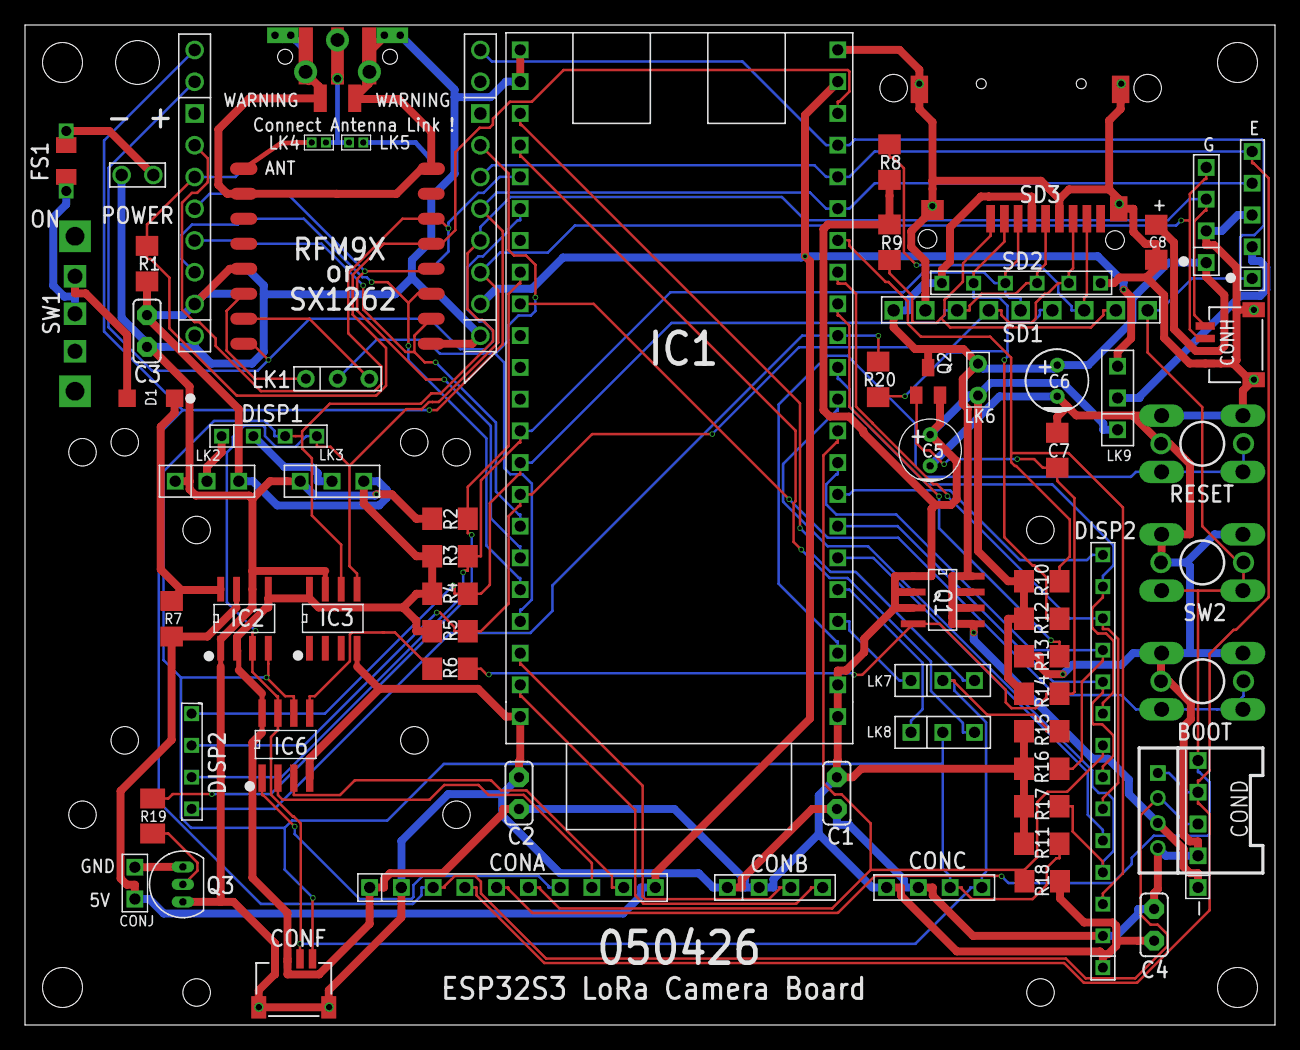
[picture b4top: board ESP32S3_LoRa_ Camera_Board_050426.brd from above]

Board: 2 copper layers, 100.0 x 80.0 mm, 79 parts (1 on the bottom side), 61 nets.
